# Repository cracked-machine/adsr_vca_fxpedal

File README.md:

# adsr_vca_fxpedal
MCU generated ADSR envelope into a LM13700 OTA VCA

## Block diagram

The audio input signal is amplitude-modulated with the ADSR waveform using the [LM13700](docs/datasheet/lm13700.pdf) in a voltage controlled amplifier (VCA) confguration.

ADSR waveform is generated via software running on a [microcontroller](docs/datasheet/stm32l432kb_datasheet.pdf) with built-in dual DAC. Two ADSR signals are generated: Inverted and Non-inverted.

ADSR generation is triggered by detecting the peak of the input signal or by manual push button. The latter can be used as a manual retrigger mechanism.

ADSR values - attack, decay, sustain and release - can be selected and then adjusted using the four potentiometers.  

An OLED display will show the current ADSR envelope shape as it is adjusted.

The raw ADSR envelope signal and VCA output are available as buffered output on 2.54mm connectors.

Both the inverted and non-inverted ADSR-modulated signals are mixed with the original "clean" audio input signal in the output stage. The mix of all three signals can be independently adjusted.

## Power Supply Scheme

This supports both guitar applications (9VDC) and modular synth (+/-12V) by switching the jumpers.

Note the 9VDC rail is split to +/-4.5VDC.

Implementation can be seen on the schematic page

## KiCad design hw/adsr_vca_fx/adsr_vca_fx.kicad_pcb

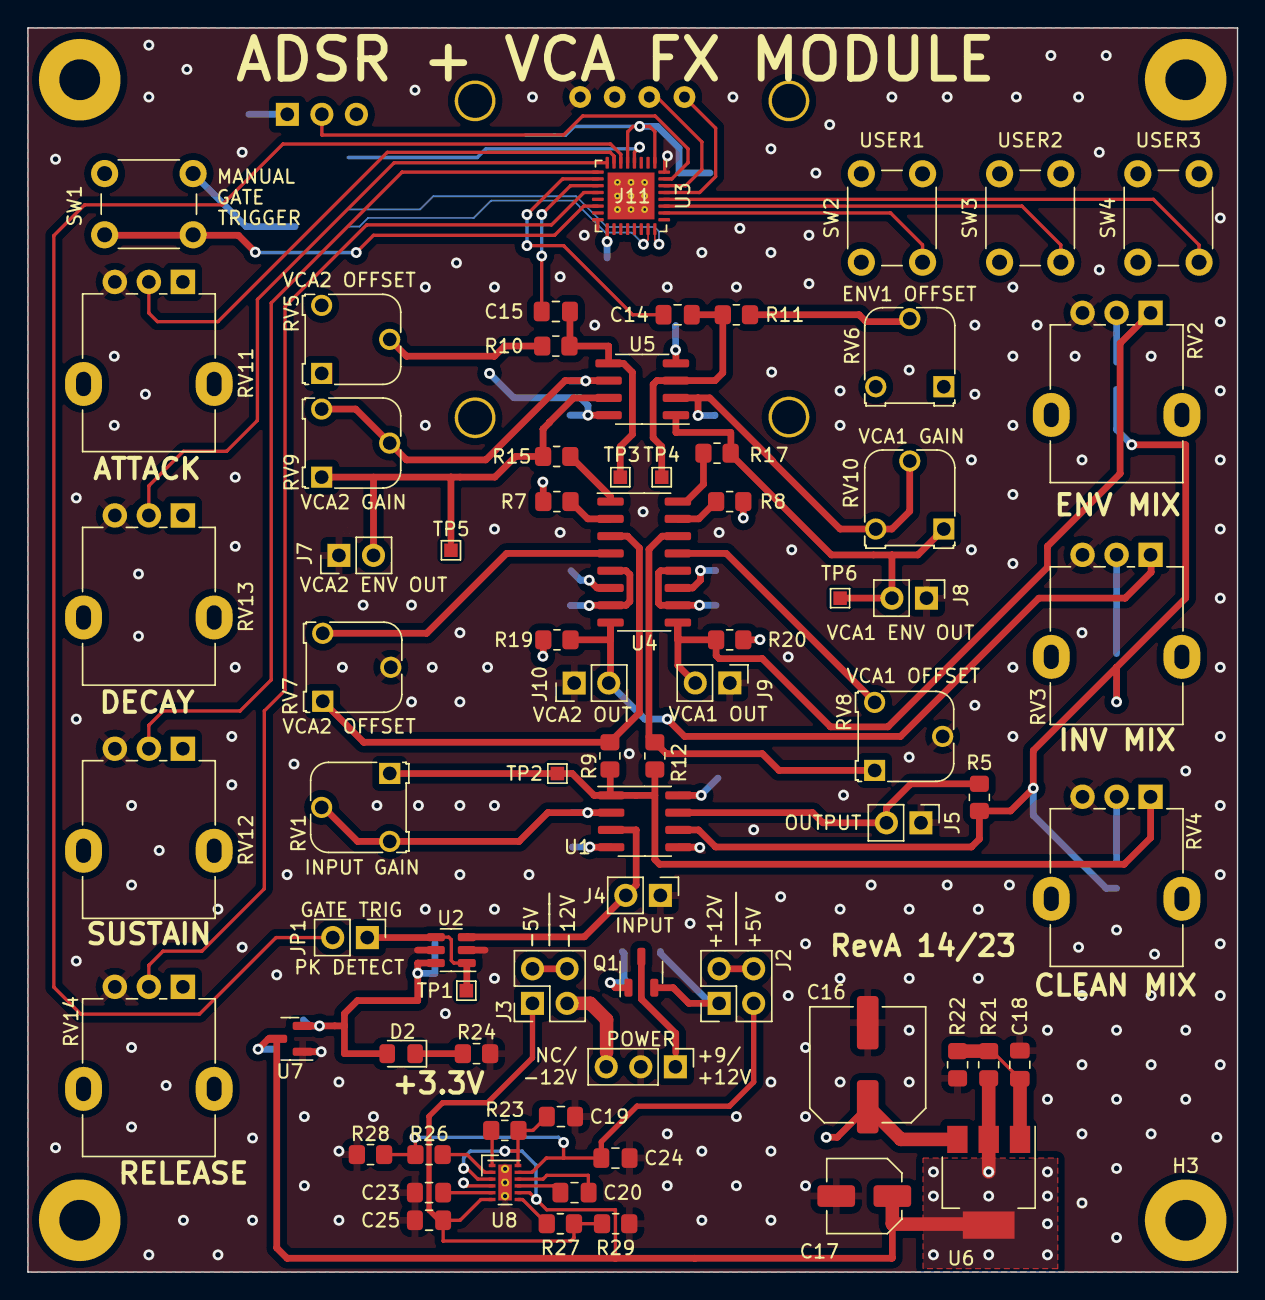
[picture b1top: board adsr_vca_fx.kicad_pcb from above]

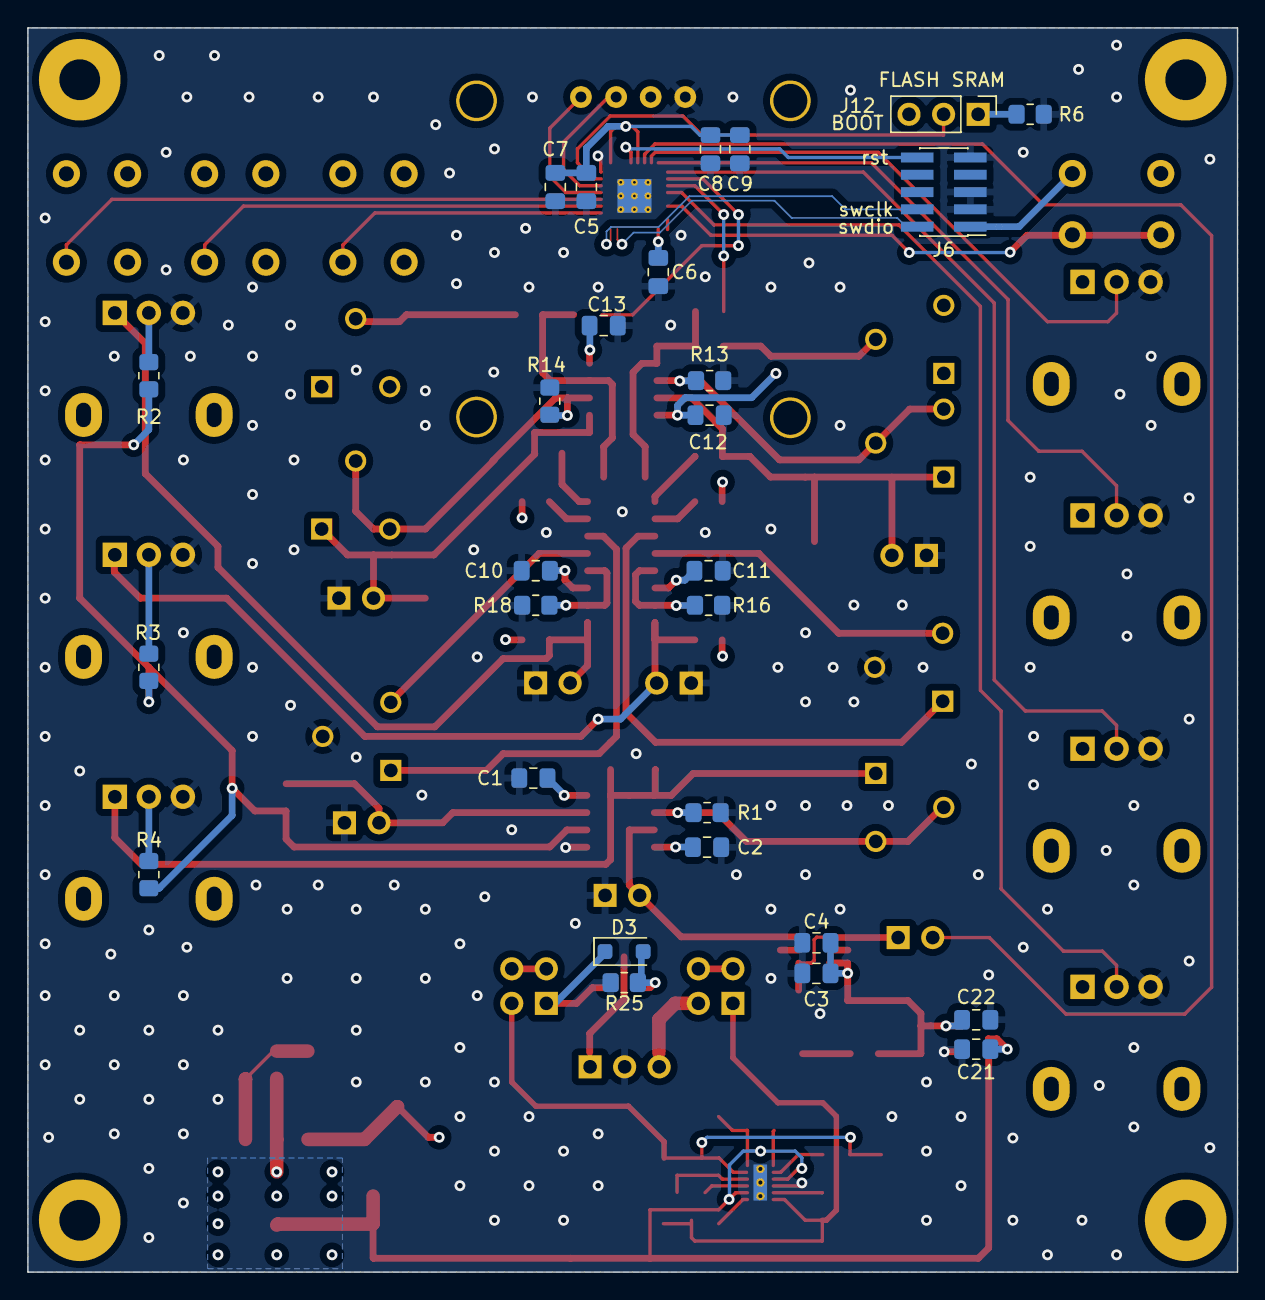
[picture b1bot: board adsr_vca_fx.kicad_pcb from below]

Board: 4 copper layers, 88.9 x 91.4 mm, 106 parts (28 on the bottom side), 66 nets.

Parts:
C1, C2, C3, C10, C11, C12, C13: 100nF; C_0805_2012Metric_Pad1.18x1.45mm_HandSolder
C4, C21: 1uF; C_0805_2012Metric_Pad1.18x1.45mm_HandSolder
C5, C6: 100nf; C_0805_2012Metric_Pad1.18x1.45mm_HandSolder
C7: 4.7uf; C_0805_2012Metric_Pad1.18x1.45mm_HandSolder
C8: 10nf; C_0805_2012Metric_Pad1.18x1.45mm_HandSolder
C9: 1uf; C_0805_2012Metric_Pad1.18x1.45mm_HandSolder
C14, C15, C22: 10uF; C_0805_2012Metric_Pad1.18x1.45mm_HandSolder
C16: 100u; C_Elec_8x5.4
C17: 20u; C_Elec_5x5.4
C18: 5.6n; C_0805_2012Metric_Pad1.18x1.45mm_HandSolder
C19: 4.7u; C_0805_2012Metric_Pad1.18x1.45mm_HandSolder
C20: 1u; C_0805_2012Metric_Pad1.18x1.45mm_HandSolder
C23: 10u; C_0805_2012Metric_Pad1.18x1.45mm_HandSolder
C24, C25: 2.2u; C_0805_2012Metric_Pad1.18x1.45mm_HandSolder
D2: RED; LED_0805_2012Metric_Pad1.15x1.40mm_HandSolder
D3: BZT52C 12V; D_SOD-123F
H1, H2, H3, H4: MountingHole; MountingHole_3mm_Pad
J1, J12: Conn_01x03; PinHeader_1x03_P2.54mm_Vertical
J2, J3: Conn_02x02_Odd_Even; PinHeader_2x02_P2.54mm_Vertical
J4: Audio Input; PinHeader_1x02_P2.54mm_Vertical
J5: Audio Output; PinHeader_1x02_P2.54mm_Vertical
J6: Conn_02x05_Odd_Even; PinHeader_2x05_P1.27mm_Vertical_SMD
J7: Envelope2 Extern; PinHeader_1x02_P2.54mm_Vertical
J8: Envelope1 Extern; PinHeader_1x02_P2.54mm_Vertical
J9: VCA1 Extern; PinHeader_1x02_P2.54mm_Vertical
J10: VCA2 Extern; PinHeader_1x02_P2.54mm_Vertical
J11: Conn_01x04; SSD1306_0.96_Oled_no_courtyard_no_silkscreen
JP1: peak detect gate; PinHeader_1x02_P2.54mm_Vertical
Q1: HX2301A PMOS; SOT-23-3
R1, R13, R14: 100R; R_0805_2012Metric_Pad1.20x1.40mm_HandSolder
R2, R3, R4, R5, R10, R11: 10k; R_0805_2012Metric_Pad1.20x1.40mm_HandSolder
R6, R23, R25: 10K; R_0805_2012Metric_Pad1.20x1.40mm_HandSolder
R7, R8: 13k; R_0805_2012Metric_Pad1.20x1.40mm_HandSolder
R9, R12: 30k; R_0805_2012Metric_Pad1.20x1.40mm_HandSolder
R15, R16, R17, R18: 30K; R_0805_2012Metric_Pad1.20x1.40mm_HandSolder
R19, R20: 5K; R_0805_2012Metric_Pad1.20x1.40mm_HandSolder
R21: 300R; R_0805_2012Metric_Pad1.20x1.40mm_HandSolder
R22: 1K; R_0805_2012Metric_Pad1.20x1.40mm_HandSolder
R24: 2K2; R_0805_2012Metric_Pad1.20x1.40mm_HandSolder
R26, R27: 470R; R_0805_2012Metric_Pad1.20x1.40mm_HandSolder
R28: 150; R_0805_2012Metric_Pad1.20x1.40mm_HandSolder
R29: 150R; R_0805_2012Metric_Pad1.20x1.40mm_HandSolder
RV1, RV7, RV8, RV9, RV10: 1K; Potentiometer_Runtron_RM-065_Vertical
RV2, RV3, RV4, RV11, RV12, RV13, RV14: PTV09A-4220F-B104; Potentiometer_Alpha_RD901F-40-00D_Single_Vertical
RV5, RV6: 10k; Potentiometer_Runtron_RM-065_Vertical
SW1, SW2, SW3, SW4: SW_Push; SW_PUSH_6mm
TP1, TP2, TP3, TP4, TP5, TP6: TestPoint; TestPoint_Pad_1.0x1.0mm
U1, U5: TL972; SOIC-8_3.9x4.9mm_P1.27mm
U2: MCP603-xCH; SOT-23-6
U3: STM32L432KBUx; QFN-32-1EP_5x5mm_P0.5mm_EP3.45x3.45mm_ThermalVias
U4: LM13700; SOIC-16_3.9x9.9mm_P1.27mm
U6: LM1117MP-ADJ; SOT-223-3_TabPin2
U7: SE8233X2; SOT-23
U8: LM27762; WSON-12-1EP_3x2mm_P0.5mm_EP1x2.65_ThermalVias

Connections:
+3.3V: C3.1, C4.1, C5.1, C6.1, C7.1, C8.1, C9.1, C22.1, D2.2 (A), J6.1, J11.2, J12.3, RV11.1, RV12.1, RV13.1, RV14.1, SW1.1, SW2.1, SW3.1, SW4.1, U2.6 (V+), U3.1 (VDD), U3.5 (VDDA), U3.17 (VDD), U7.2 (VO)
/ADSRPots/env_in.attack: RV11.2, U3.7 (PA1)
/ADSRPots/env_in.decay: RV13.2, U3.8 (PA2)
/ADSRPots/env_in.release: RV14.2, U3.12 (PA6)
/ADSRPots/env_in.sustain: RV12.2, U3.9 (PA3)
/AudioInput/audio_out: R9.1, R12.1, RV1.1, RV4.1, TP2.1, U1.1
/AudioInput/peak_detect_out: JP1.1 (A), TP1.1, U2.1, U2.4 (-)
/AudioOutput/audio_in1: J9.2, R20.2, RV2.1, U4.9
/AudioOutput/audio_in2: J10.2, R19.2, RV3.1, U4.8
/EnvelopeGenerator/adsr_env_out1: C14.1, U3.10 (PA4)
/EnvelopeGenerator/adsr_env_out2: C15.1, U3.11 (PA5)
/EnvelopeGenerator/boot0: J12.2, U3.31 (PH3)
/EnvelopeGenerator/displaybus.scl: J11.4, U3.29 (PB6)
/EnvelopeGenerator/displaybus.sda: J11.3, U3.30 (PB7)
/EnvelopeGenerator/manual_gate_cv: SW1.2, U3.14 (PB0)
/EnvelopeGenerator/peak_detect_gatecv: JP1.2 (B), U3.6 (PA0)
/EnvelopeGenerator/reset: J6.10, U3.4 (NRST)
/EnvelopeGenerator/swclk: J6.4, U3.24 (PA14)
/EnvelopeGenerator/swdio: J6.2, U3.23 (PA13)
/EnvelopeGenerator/user_btn1: SW2.2, U3.26 (PB3)
/EnvelopeGenerator/user_btn2: SW3.2, U3.27 (PB4)
/EnvelopeGenerator/user_btn3: SW4.2, U3.28 (PB5)
/PowerSupply/+5V: C17.1, C19.1, C21.1, R21.1, R23.1, U6.2 (VO), U7.3 (VI), U8.3 (VIN), U8.8 (EN-), U8.12 (EN+)
/PowerSupply/-5V: C25.1, J3.1, R27.2, R29.1, U8.6 (OUT-)
/PowerSupply/Dual Rail Regulated Charge Pump/CP_VOUT_POS: C24.1, J2.3, R26.2, R28.1, U8.11 (OUT+)
/PowerSupply/PolarityProtection/VOUT: C16.1, D3.1 (K), J2.1, Q1.2 (S), U6.3 (VI)
/VoltageControlledAmplifier/lindiode1: R7.1, U4.2 (DIODE_BIAS)
/VoltageControlledAmplifier/lindiode2: R8.1, U4.15 (DIODE_BIAS)
GND: C1.2, C2.1, C3.2, C4.2, C5.2, C6.2, C7.2, C8.2, C9.2, C10.2, C11.1, C12.2, C13.1, C16.2, C17.2, C18.2, C19.2, C21.2, C22.2, C23.2, C24.2, C25.2, J1.2, J4.1, J5.1, J6.3, J6.5, J6.9, J7.1, J8.1, J9.1, J10.1, J11.1, R1.1, R6.2, R13.1, R14.1, R16.1, R18.1, R22.2, R24.2, R25.2, R28.2, R29.2, RV2.3, RV3.3, RV4.3, RV7.2, RV8.2, RV11.3, RV12.3, RV13.3, RV14.3, U1.5 (+), U2.2 (V-), U2.5 (~CS), U3.16 (VSS), U3.32 (VSS), U3.33 (VSS), U7.1 (GND), U8.4 (GND), U8.13 (PAD)
unnamed: D2.1 (K), R24.1
unnamed: D3.2 (A), Q1.1 (G), R25.1
unnamed: J4.2, U1.3 (+), U2.3 (+)
unnamed: J5.2, R5.2, U1.7
unnamed: J7.2, R15.2, RV9.1, TP5.1, U5.7
unnamed: J8.2, R17.2, RV10.1, TP6.1, U5.1
unnamed: J12.1, R6.1
unnamed: R2.1, RV2.2
unnamed: R3.1, RV3.2
unnamed: R4.1, RV4.2
unnamed: R10.1, RV5.2
unnamed: R11.1, RV6.2
unnamed: R15.1, U4.1
unnamed: R16.2, U4.5, U4.7
unnamed: R17.1, U4.16
unnamed: R18.2, U4.10, U4.12
unnamed: R1.2, RV1.2, RV1.3, U1.2 (-)
unnamed: R2.2, R3.2, R4.2, R5.1, U1.6 (-)
unnamed: R12.2, RV8.1, U4.14 (+)
unnamed: RV8.3, U4.13 (-)
unnamed: R9.2, RV7.1, U4.3 (+)
unnamed: RV7.3, U4.4 (-)
unnamed: C14.2, R11.2, TP4.1, U5.3 (+)
unnamed: R14.2, RV10.2, RV10.3, U5.2 (-)
unnamed: C15.2, R10.2, TP3.1, U5.5 (+)
unnamed: R13.2, RV9.2, RV9.3, U5.6 (-)
unnamed: C18.1, R21.2, R22.1, U6.1 (ADJ)
unnamed: C20.2, U8.10 (C+)
unnamed: C20.1, U8.9 (C-)
unnamed: C23.1, U8.5 (CP)
unnamed: R26.1, U8.2 (FB+)
unnamed: R27.1, U8.7 (FB-)
unnamed: R23.2, U8.1 (PGOOD)
VDD: J1.1, Q1.3 (D)
VDDA: C1.1, C10.1, C12.1, J2.2, J2.4, R7.2, R8.2, RV5.1, RV6.1, U1.8 (V+), U4.11 (V+), U5.8 (V+)
VSS: J1.3, J3.3
VSSA: C2.2, C11.2, C13.2, J3.2, J3.4, R19.1, R20.1, RV5.3, RV6.3, U1.4 (V-), U4.6 (V-), U5.4 (V-)

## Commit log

2023-03-18 first schema draft
2023-03-18 testing earlevel adsr lib
2023-03-19 modified design into normal/inverted envlope
2023-03-21 renamed sheet
2023-03-21 added OLED footprint
2023-03-21 updated text labels
2023-03-21 updated pdf
2023-03-25 first draft layout
2023-03-26 tidied up layout
2023-03-26 updated layout
2023-04-03 completed layout
2023-04-28 RevB; simplified power supply
